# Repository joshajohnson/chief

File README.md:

# chief

A macropad designed by Bing Xu

Status: Untested

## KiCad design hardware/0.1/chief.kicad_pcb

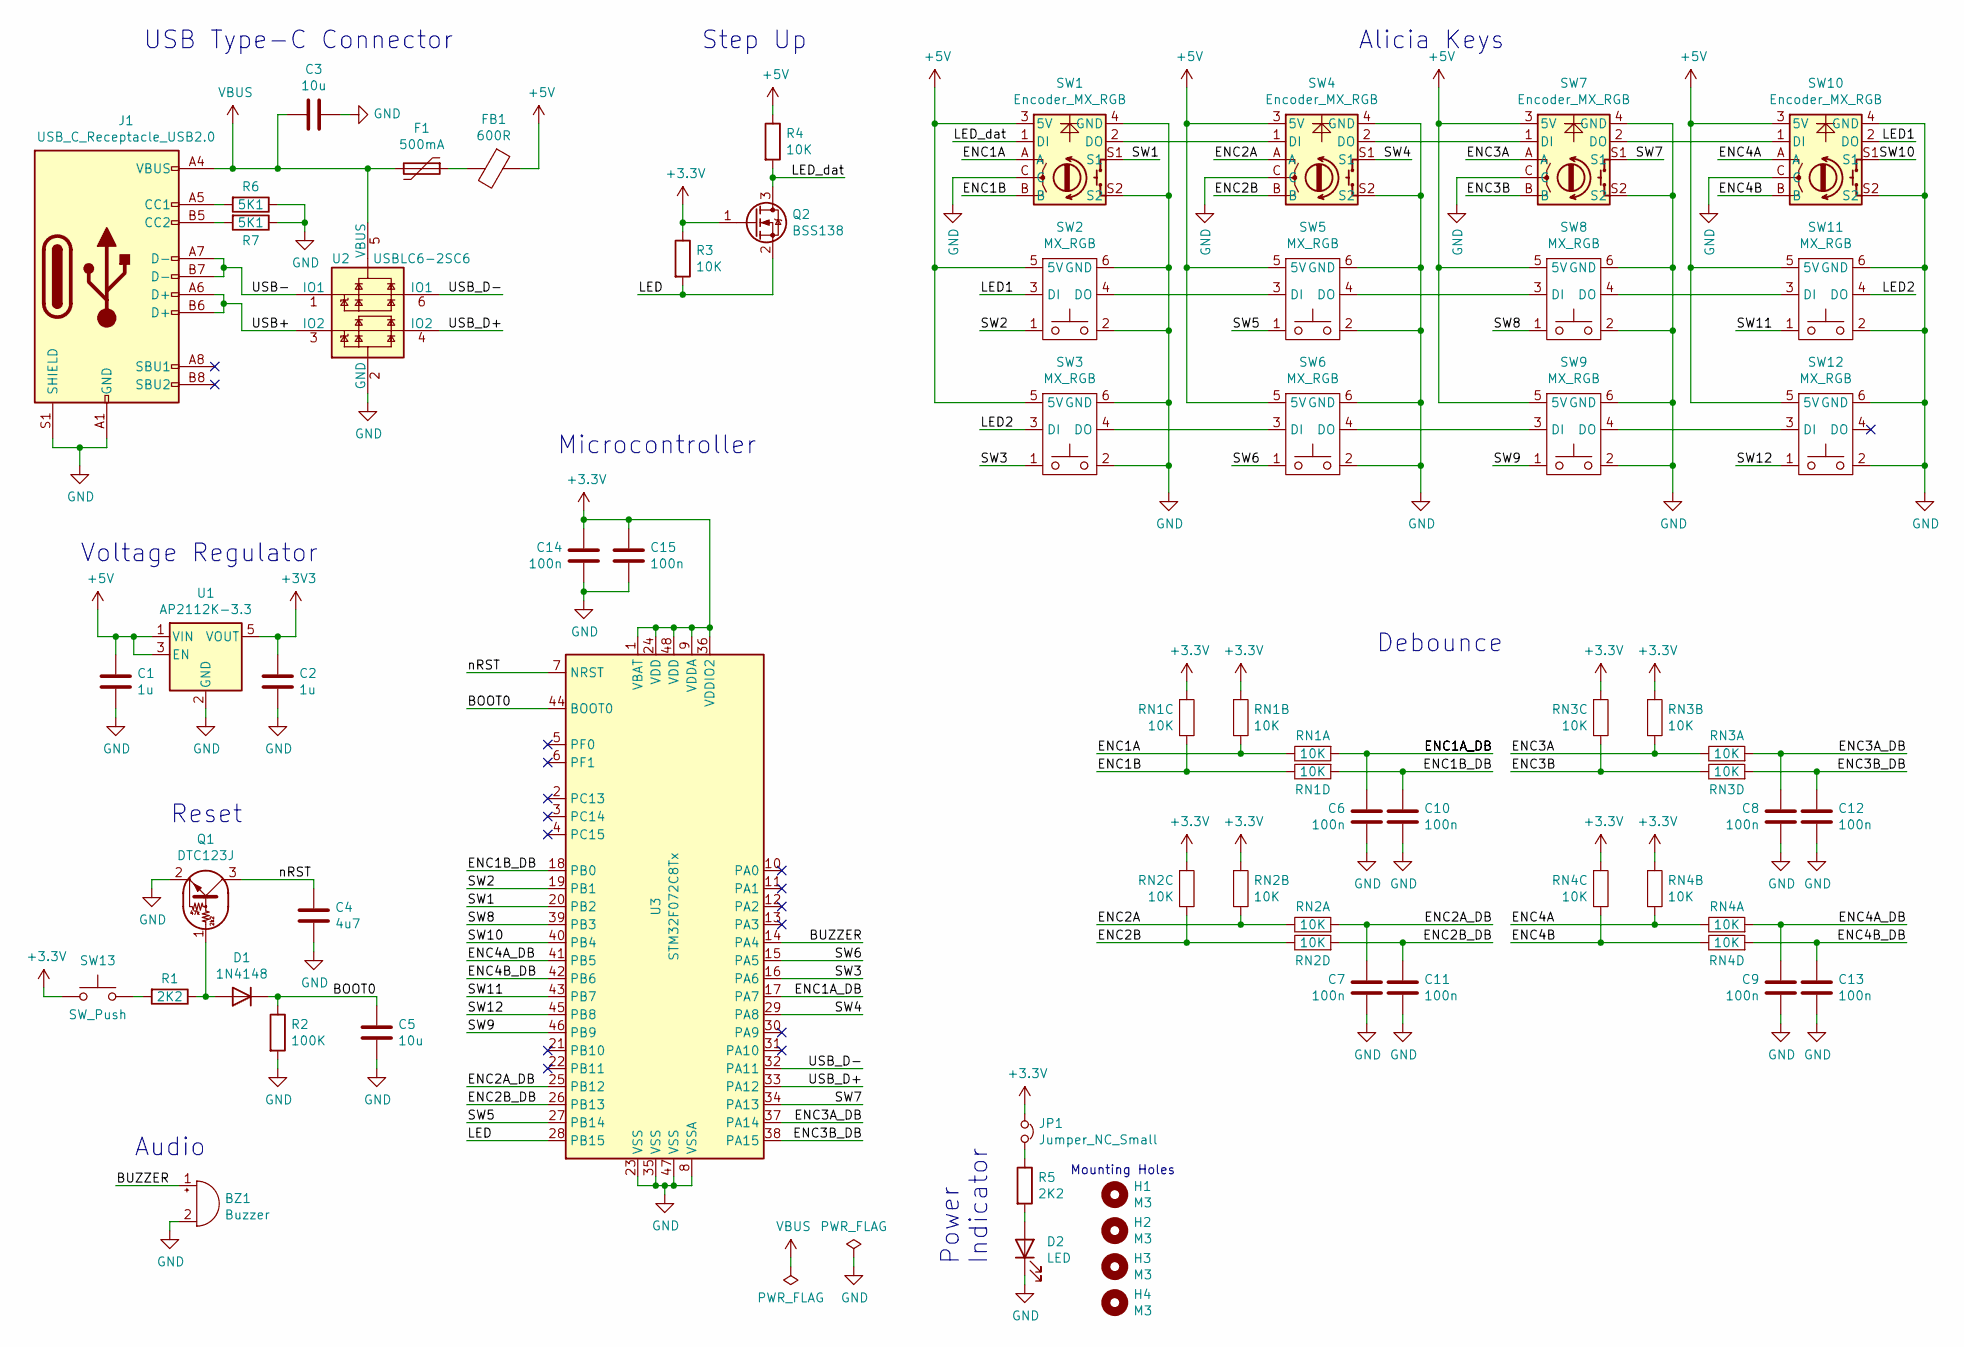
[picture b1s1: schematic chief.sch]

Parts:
BZ1: Buzzer; Buzzer_Murata_PKMCS0909E4000-R1
C1, C2: 1u; C_0603_1608Metric
C3, C5: 10u; C_0603_1608Metric
C4: 4u7; C_0603_1608Metric
C6, C7, C8, C9, C10, C11, C12, C13, C14, C15: 100n; C_0603_1608Metric
D1: 1N4148; D_SOD-123
D2: LED; LED_0603_1608Metric
F1: 500mA; Fuse_0603_1608Metric
FB1: 600R; Ferrite_Bead_0603
H1, H2, H3, H4: M3; MountingHole_3.2mm_M3
J1: USB_C_Receptacle_USB2.0; USB_C_U262-161N-4BVC11
JP1: Jumper_NC_Small; SolderJumper-2_P1.3mm_Bridged_RoundedPad1.0x1.5mm
Q1: DTC123J; SOT-23
Q2: BSS138; SOT-23
R1, R5: 2K2; R_0603_1608Metric
R2: 100K; R_0603_1608Metric
R3, R4: 10K; R_0603_1608Metric
R6, R7: 5K1; R_0603_1608Metric
RN1, RN2, RN3, RN4: 10K; R_Array_Convex_4x0603
SW1, SW4, SW7, SW10: Encoder_MX_RGB; MX_KEYSWITCH_ENCODER_RGB
SW2, SW3, SW5, SW6, SW8, SW9, SW11, SW12: MX_RGB; MX_KEYSWITCH_RGB
SW13: SW_Push; Panasonic_EVQPUL_EVQPUC
U1: AP2112K-3.3; SOT-23-5
U2: USBLC6-2SC6; SOT-23-6
U3: STM32F072C8Tx; LQFP-48_7x7mm_P0.5mm

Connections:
+5V: C1.1, FB1.1, R4.1, SW1.3 (5V), SW2.5 (5V), SW3.5 (5V), SW4.3 (5V), SW5.5 (5V), SW6.5 (5V), SW7.3 (5V), SW8.5 (5V), SW9.5 (5V), SW10.3 (5V), SW11.5 (5V), SW12.5 (5V), U1.1 (VIN), U1.3 (EN); also elsewhere on the board
/BKLT: SW12.4 (DO); also elsewhere on the board
/BOOT0: C5.1, D1.1 (K), R2.1, U3.44 (BOOT0)
/BUZZER: BZ1.1 (-), U3.14 (PA4)
/ENC1A: RN1.5, RN1.6, SW1.A
/ENC1A_DB: C6.1, RN1.4, U3.17 (PA7)
/ENC1B: RN1.7, RN1.8, SW1.B
/ENC1B_DB: C10.1, RN1.1, U3.18 (PB0)
/ENC2A: RN2.5, RN2.6, SW4.A
/ENC2A_DB: C7.1, RN2.4, U3.25 (PB12)
/ENC2B: RN2.7, RN2.8, SW4.B
/ENC2B_DB: C11.1, RN2.1, U3.26 (PB13)
/ENC3A: RN3.5, RN3.6, SW7.A
/ENC3A_DB: C8.1, RN3.4, U3.37 (PA14)
/ENC3B: RN3.7, RN3.8, SW7.B
/ENC3B_DB: C12.1, RN3.1, U3.38 (PA15)
/ENC4A: RN4.5, RN4.6, SW10.A
/ENC4A_DB: C9.1, RN4.4, U3.41 (PB5)
/ENC4B: RN4.7, RN4.8, SW10.B
/ENC4B_DB: C13.1, RN4.1, U3.42 (PB6)
/LED: Q2.2 (S), R3.2, U3.28 (PB15)
/LED1: SW2.3 (DI), SW10.2 (DO)
/LED2: SW3.3 (DI), SW11.4 (DO)
/LED_dat: Q2.3 (D), R4.2, SW1.1 (DI)
/SW1: SW1.S1, U3.20 (PB2)
/SW2: SW2.1, U3.19 (PB1)
/SW3: SW3.1, U3.16 (PA6)
/SW4: SW4.S1, U3.29 (PA8)
/SW5: SW5.1, U3.27 (PB14)
/SW6: SW6.1, U3.15 (PA5)
/SW7: SW7.S1, U3.34 (PA13)
/SW8: SW8.1, U3.39 (PB3)
/SW9: SW9.1, U3.46 (PB9)
/SW10: SW10.S1, U3.40 (PB4)
/SW11: SW11.1, U3.43 (PB7)
/SW12: SW12.1, U3.45 (PB8)
/USB+: J1.A6 (D+), J1.B6 (D+), U2.3 (IO2)
/USB-: J1.A7 (D-), J1.B7 (D-), U2.1 (IO1)
/USB_D+: U2.4 (IO2), U3.33 (PA12)
/USB_D-: U2.6 (IO1), U3.32 (PA11)
/nRST: C4.1, Q1.3 (C), U3.7 (NRST)
GND: BZ1.2 (+), C1.2, C2.2, C3.2, C4.2, C5.2, C6.2, C7.2, C8.2, C9.2, C10.2, C11.2, C12.2, C13.2, C14.2, C15.2, D2.1 (K), J1.A1 (GND), J1.A12 (GND), J1.B1 (GND), J1.B12 (GND), J1.S1 (SHIELD), Q1.2 (E), R2.2, R6.1, R7.1, SW1.4 (GND), SW1.C, SW1.S2, SW2.2, SW2.6 (GND), SW3.2, SW3.6 (GND), SW4.4 (GND), SW4.C, SW4.S2, SW5.2, SW5.6 (GND), SW6.2, SW6.6 (GND), SW7.4 (GND), SW7.C, SW7.S2, SW8.2, SW8.6 (GND), SW9.2, SW9.6 (GND), SW10.4 (GND), SW10.C, SW10.S2, SW11.2, SW11.6 (GND), SW12.2, SW12.6 (GND), U1.2 (GND), U2.2 (GND), U3.8 (VSSA), U3.23 (VSS), U3.35 (VSS), U3.47 (VSS); also elsewhere on the board
unnamed: D1.2 (A), Q1.1 (B), R1.1
unnamed: D2.2 (A), R5.2
unnamed: F1.1, FB1.2
unnamed: J1.A5 (CC1), R6.2
unnamed: J1.B5 (CC2), R7.2
unnamed: JP1.2, R5.1
unnamed: R1.2, SW13.2
unnamed: SW1.2 (DO), SW4.1 (DI)
unnamed: SW2.4 (DO), SW5.3 (DI)
unnamed: SW3.4 (DO), SW6.3 (DI)
unnamed: SW4.2 (DO), SW7.1 (DI)
unnamed: SW5.4 (DO), SW8.3 (DI)
unnamed: SW6.4 (DO), SW9.3 (DI)
unnamed: SW7.2 (DO), SW10.1 (DI)
unnamed: SW8.4 (DO), SW11.3 (DI)
unnamed: SW9.4 (DO), SW12.3 (DI)
VBUS: C3.1, F1.2, J1.A4 (VBUS), J1.A9 (VBUS), J1.B4 (VBUS), J1.B9 (VBUS), U2.5 (VBUS)

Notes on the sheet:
Mounting Holes
Voltage Regulator
USB Type-C Connector
Reset
Audio
Step Up
Power Indicator
Debounce
Alicia Keys
Microcontroller

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
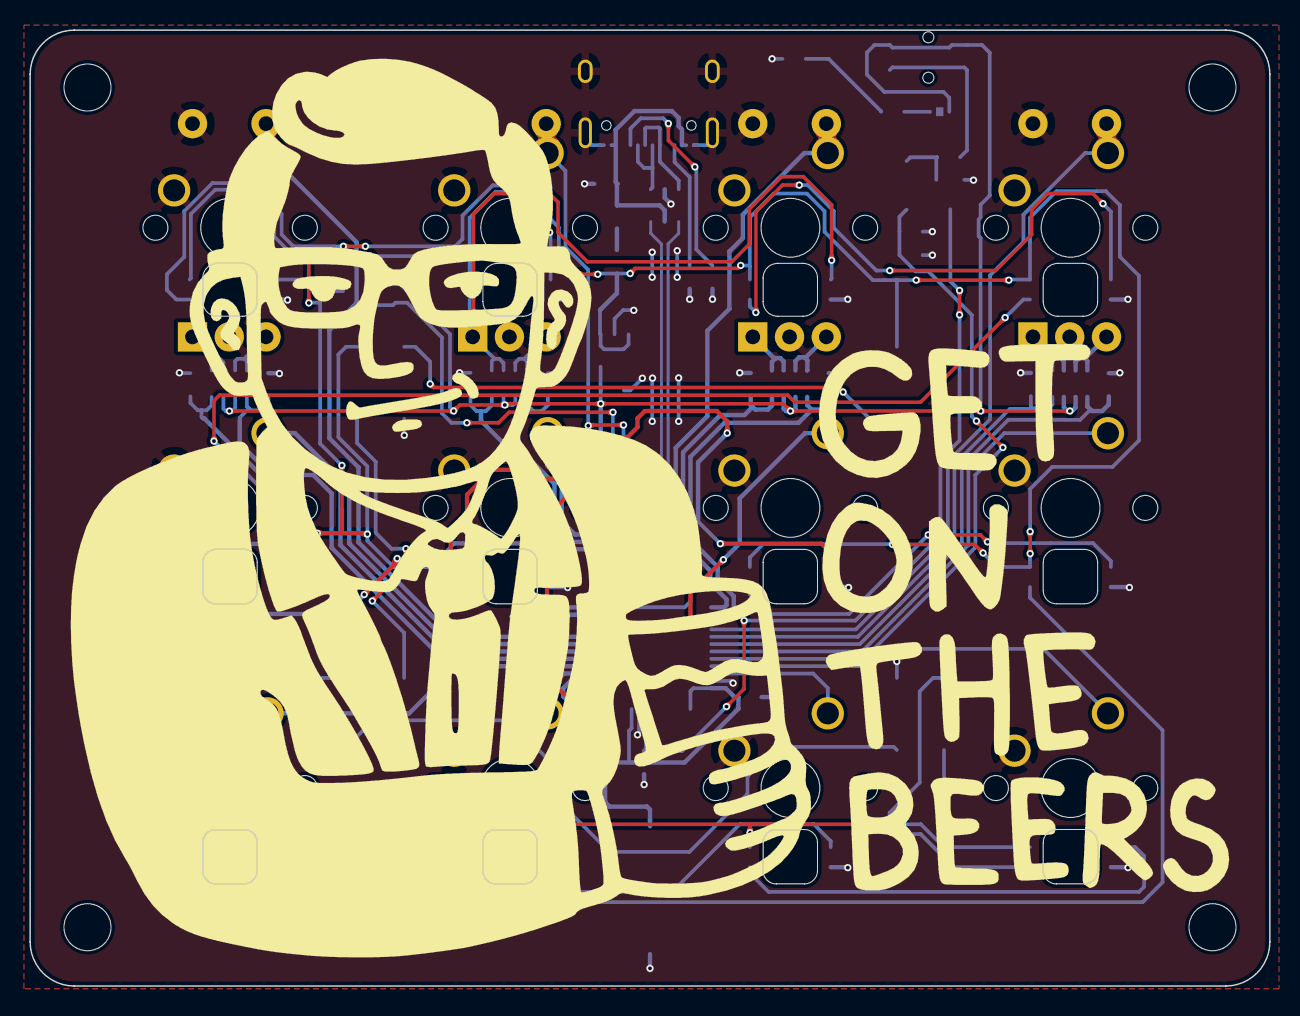
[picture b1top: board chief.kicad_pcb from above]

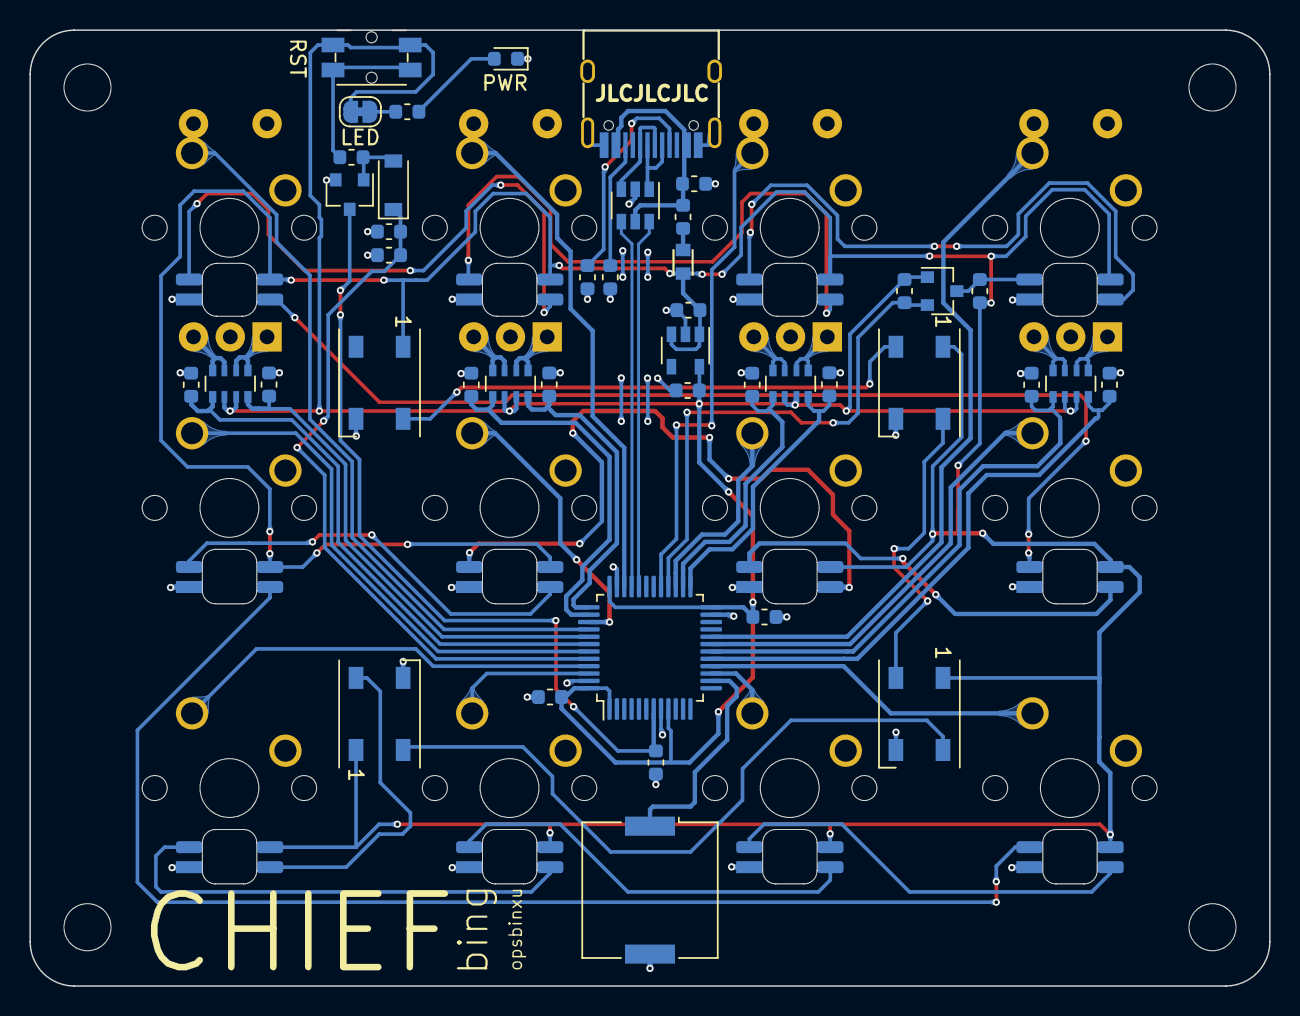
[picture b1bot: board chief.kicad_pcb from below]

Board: 2 copper layers, 84.3 x 65.0 mm, 60 parts (43 on the bottom side), 63 nets.

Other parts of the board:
D3, D4, D5, D6: WS2812B; LED_WS2812B_PLCC4_5.0x5.0mm_P3.2mm
H5: dan; danandrews

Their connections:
+5V: D3.1, D4.1, D5.1, D6.1; also elsewhere on the board
/BKLT: D3.4; also elsewhere on the board
GND: D3.3, D4.3, D5.3, D6.3; also elsewhere on the board
unnamed: D3.2, D4.4
unnamed: D4.2, D5.4
unnamed: D5.2, D6.4

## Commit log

2020-06-25 Update schematics
2020-06-25 Associate footprints
2020-06-26 trying to fix josh kicad lib
2020-06-26 Update josh-kicad-lib
2020-06-26 schematic review
2020-06-26 parts ready to layout
2020-06-27 Layout complete. ENC2/ENC2DB swapped with ENC3/ENC3DB to match resistor labelling
2020-06-29 Footprints arranged and layout attempted
2020-06-30 sorry Bing
2020-06-30 moar layout
2020-06-30 LEDs connected, adjustments to LED/text/image position
2020-07-01 LED positioning
2020-07-01 More spacing from holes
2020-07-01 Revert "More spacing from holes"
    This reverts commit 336c5e49fdea355c48cb6621cc449f3f6412bd08.
2020-07-01 CAD for casing
2020-07-02 Casing with speaker holes
2020-07-04 thumb fix, LED position adjusted and rewired
2020-07-04 Fix 1 unconnected ground
2020-07-04 Fix feet
2020-07-05 off to fab
2020-07-17 Prelim work on code
